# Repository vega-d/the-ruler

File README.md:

# the-ruler
it's a pcb ruler. It looks kinda nice.

You can take a zip file and upload it to your PCB maker to get a couple of them yourself. 

Designed in KiCad, editable and hackable

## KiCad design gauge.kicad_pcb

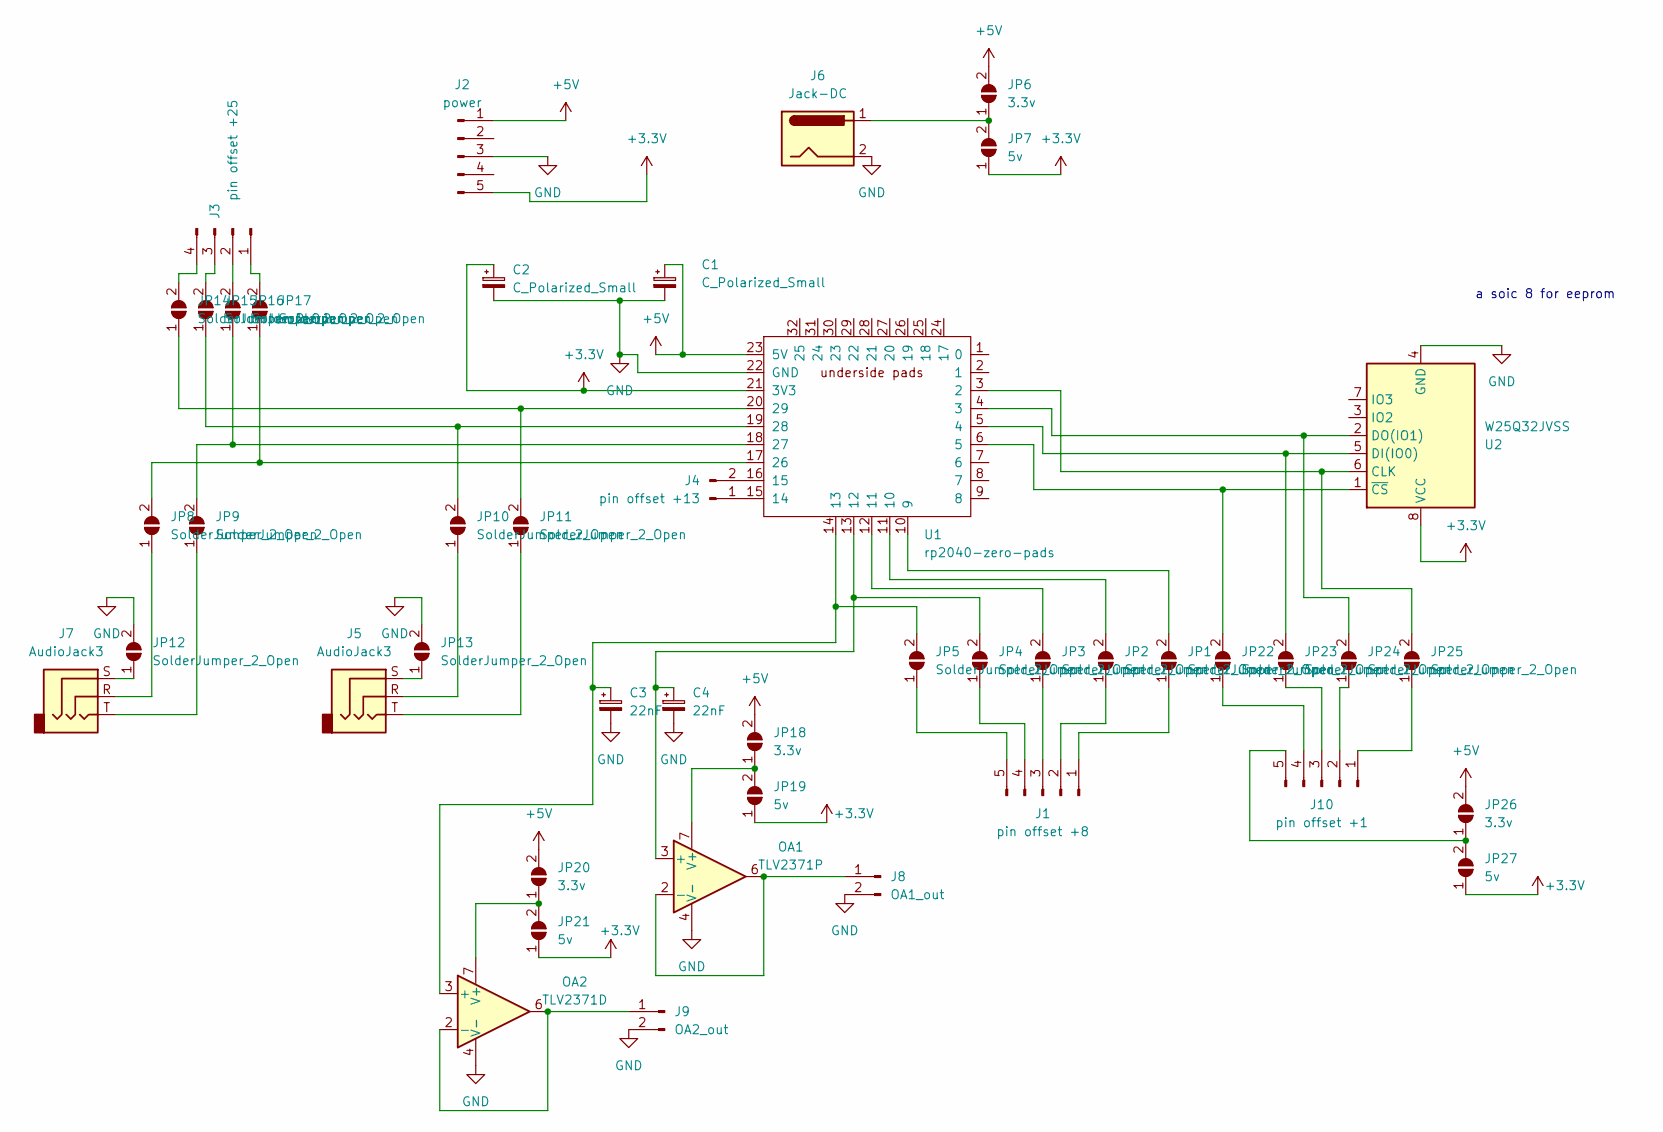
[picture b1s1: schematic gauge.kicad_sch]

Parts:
C1, C2: C_Polarized_Small; CP_Radial_D4.0mm_P1.50mm
C3, C4: 22nF; CP_Radial_D4.0mm_P1.50mm
J1: pin offset +8; PinHeader_1x05_P2.54mm_Vertical
J2: power; PinHeader_1x05_P2.54mm_Vertical
J3: pin offset +25; PinHeader_1x04_P2.54mm_Vertical
J4: pin offset +13; PinHeader_1x02_P2.54mm_Vertical
J5, J7: AudioJack3; Jack_3.5mm_CUI_SJ-3523-SMT_Horizontal
J6: Jack-DC; BarrelJack_SwitchcraftConxall_RAPC10U_Horizontal
J8: OA1_out; PinHeader_1x02_P2.54mm_Vertical
J9: OA2_out; PinHeader_1x02_P2.54mm_Vertical
J10: pin offset +1; PinHeader_1x05_P2.54mm_Vertical
JP1, JP2, JP3, JP4, JP5, JP8, JP9, JP10, JP11, JP12, JP13, JP14, JP15, JP16, JP17, JP22, JP23, JP24, JP25: SolderJumper_2_Open; SolderJumper-2_P1.3mm_Open_Pad1.0x1.5mm
JP6, JP18, JP20, JP26: 3.3v; SolderJumper-2_P1.3mm_Open_Pad1.0x1.5mm
JP7, JP19, JP21, JP27: 5v; SolderJumper-2_P1.3mm_Open_Pad1.0x1.5mm
OA1: TLV2371P; DIP-8_W7.62mm
OA2: TLV2371D; SOIC-8_3.9x4.9mm_P1.27mm
U1: rp2040-zero-pads; rp2040-zero-tht-pads-cutout
U2: W25Q32JVSS; SOIC-8_5.23x5.23mm_P1.27mm

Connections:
+3.3V: C2.1, J2.5, JP7.1 (A), JP19.1 (A), JP21.1 (A), JP27.1 (A), U1.21 (3V3), U2.8 (VCC)
+5V: C1.1, J2.1, JP6.2 (B), JP18.2 (B), JP20.2 (B), JP26.2 (B), U1.23 (5V)
GND: C1.2, C2.2, C3.2, C4.2, J2.3, J6.2, J8.2, J9.2, JP12.2 (B), JP13.2 (B), OA1.4 (V-), OA2.4 (V-), U1.22 (GND), U1.33 (GND), U2.4 (GND)
unnamed: J1.1, JP1.1 (A)
unnamed: J1.2, JP2.1 (A)
unnamed: J1.3, JP3.1 (A)
unnamed: J1.4, JP4.1 (A)
unnamed: J1.5, JP5.1 (A)
unnamed: J3.1, JP17.2 (B)
unnamed: J3.2, JP16.2 (B)
unnamed: J3.3, JP15.2 (B)
unnamed: J3.4, JP14.2 (B)
unnamed: J4.1, U1.15 (14)
unnamed: J4.2, U1.16 (15)
unnamed: J8.1, OA1.2 (-), OA1.6
unnamed: J9.1, OA2.2 (-), OA2.6
unnamed: J10.1, JP25.1 (A)
unnamed: J10.2, JP24.1 (A)
unnamed: J10.3, JP23.1 (A)
unnamed: J10.4, JP22.1 (A)
unnamed: J10.5, JP26.1 (A), JP27.2 (B)
unnamed: JP1.2 (B), U1.10 (9)
unnamed: JP2.2 (B), U1.11 (10)
unnamed: JP3.2 (B), U1.12 (11)
unnamed: C4.1, JP4.2 (B), OA1.3 (+), U1.13 (12)
unnamed: C3.1, JP5.2 (B), OA2.3 (+), U1.14 (13)
unnamed: J6.1, JP6.1 (A), JP7.2 (B)
unnamed: J7.R, JP8.1 (A)
unnamed: J7.T, JP9.1 (A)
unnamed: J5.R, JP10.1 (A)
unnamed: JP10.2 (B), JP15.1 (A), U1.19 (28)
unnamed: J5.T, JP11.1 (A)
unnamed: JP11.2 (B), JP14.1 (A), U1.20 (29)
unnamed: J7.S, JP12.1 (A)
unnamed: J5.S, JP13.1 (A)
unnamed: JP9.2 (B), JP16.1 (A), U1.18 (27)
unnamed: JP8.2 (B), JP17.1 (A), U1.17 (26)
unnamed: JP18.1 (A), JP19.2 (B), OA1.7 (V+)
unnamed: JP20.1 (A), JP21.2 (B), OA2.7 (V+)
unnamed: JP22.2 (B), U1.6 (5), U2.1 (~CS)
unnamed: JP23.2 (B), U1.5 (4), U2.5 (DI(IO0))
unnamed: JP24.2 (B), U1.4 (3), U2.2 (DO(IO1))
unnamed: JP25.2 (B), U1.3 (2), U2.6 (CLK)

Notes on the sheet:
a soic 8 for eeprom

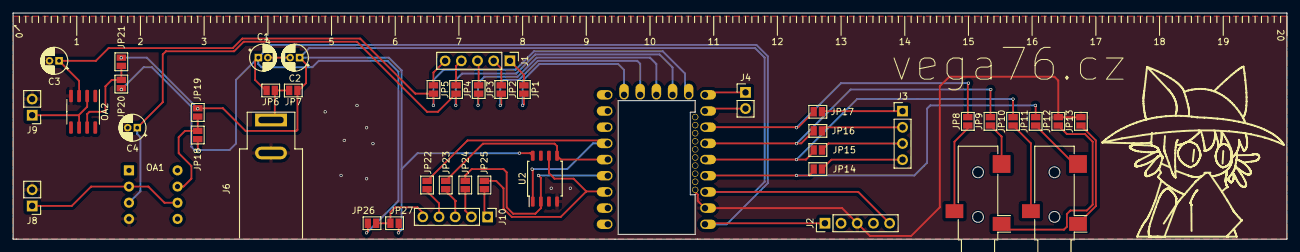
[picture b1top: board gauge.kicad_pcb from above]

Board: 2 copper layers, 200.0 x 35.5 mm, 45 parts (0 on the bottom side), 43 nets.

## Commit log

2024-02-19 the ruler V2! Now better, stronger, faster
2024-02-20 attempt to sign the commit
2024-02-20 attempt to sign a commit v2
